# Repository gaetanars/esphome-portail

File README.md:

# esphome-portail

Pilotage d'un portail battant **FAAC E045S** avec un ESP32 sous [ESPHome](https://esphome.io) : commande
ouvrir / fermer / stop / ouverture piéton, et retour d'état et de position dans Home Assistant, y compris pour les
mouvements déclenchés par la télécommande ou un bouton.

> ⚠️ **Sécurité** : la carte et la sortie LAMP sont en **230 V~**. Coupez l'alimentation avant toute intervention
> et faites intervenir une personne qualifiée. Un portail motorisé est une machine dangereuse : vérifiez le
> fonctionnement des sécurités (cellules, détection d'obstacle) après toute modification.

## Matériel

- ESP32 de type WROOM / `esp32dev` (GPIO16/17 sont indisponibles sur les modules WROVER à PSRAM).
- 2 relais (contact NO) : simulent les entrées OP-A et OP-B.
- 1 optocoupleur compatible 24 V : lit la sortie W.L.
- 1 module de détection 230 V (isolé) : lit la sortie LAMP.

### Exemples de références

Exemples non exhaustifs, à vérifier (tension, brochage, logique) avant achat : aucun n'est imposé.

| Rôle | Exemples |
|---|---|
| ESP32 | Espressif ESP32-DevKitC-32E (module WROOM-32E), ESP32 DevKit V1 (DOIT) – tout module WROOM sur carte `esp32dev` |
| Relais OP-A / OP-B | Module 2 relais 5 V à optocoupleur (relais SRD-05VDC-SL-C, contact NO) ; ou relais miniature 5 V + transistor |
| Lecture W.L. (24 V) | Module optocoupleur PC817 / EL817 (entrée 3,6–30 V, sortie collecteur vers GPIO) |
| Lecture LAMP (230 V~) | Module de détection tension secteur à optocoupleur (« AC 220 V optocoupler isolation board », sortie 3,3–5 V) ; ou relais miniature à bobine 230 V~ (famille Finder 40.31) dont le contact NO est lu par le GPIO |
| Alimentation ESP32 | Depuis la sortie 24 V de la carte (J9 – 17/18) via un convertisseur abaisseur 24 V → 5 V (MP1584, LM2596) ; ou module secteur isolé Hi-Link HLK-PM01 (5 V) |

Points d'attention :

- Beaucoup de modules relais sont **actifs à l'état bas** : vérifier la fiche et ajouter `inverted: true` sur les `switch` si besoin.
- Les modules d'entrée doivent être **isolés galvaniquement** (optocoupleur) ; ne jamais relier le 230 V ni le 24 V directement à un GPIO.
- Les capteurs analogiques de tension (type ZMPT101B) ne conviennent pas : il faut une sortie logique tout ou rien.
- Si la sortie du module est active à l'état haut, adapter `inverted` sur les `binary_sensor` `wl` et `lamp`.

## Câblage

Notice FAAC E045S, réf. 532373 Rev.A, FW 4.0 (non redistribuée : copyright FAAC, `docs/*.pdf` est ignoré par git).

| Fonction | Borne carte | Côté ESP32 | GPIO |
|---|---|---|---|
| OP-A (ouverture totale) | J3 – 9 | relais A, NO | GPIO16 |
| OP-B (ouverture piéton) | J3 – 10 | relais B, NO | GPIO17 |
| Commun « - » des commandes | J9 – 15/16 | commun des relais | – |
| W.L. (collecteur ouvert, 24 V 3 W, 100 mA max) | J11 – 20 | optocoupleur (+24 V : J9 – 17/18) | GPIO25 |
| LAMP (230 V~ 60 W) | J2 – 7/8 | module de détection 230 V | GPIO26 |

Les broches se changent via les `substitutions` de `portail.yaml`.

## Carte dédiée (optionnel)

`hardware/` contient une carte unique (KiCad 10) qui remplace les modules du commerce : ESP32-WROOM-32UE (antenne
déportée), 2 relais, optos W.L. et LAMP, alimentation 24 V → 5 V → 3,3 V et USB-C pour le premier flash. Le brochage
reste celui de `portail.yaml` (GPIO16/17/25/26) : aucun changement de firmware. Voir `hardware/README.md`.

## Réglages requis sur la carte

| Paramètre | Valeur | Raison |
|---|---|---|
| `Lo` (logique) | `E` ou `EP` | Seules logiques supportées (OPEN stoppe/inverse). `A`/`AP`/`SP` : fermeture auto non pilotée ; `b`/`C` : non supportées. |
| `Sp` (sortie W.L.) | `00` (défaut) | Fixe = ouverture/ouvert/pause, clignotante = fermeture, éteinte = fermé. |
| `PF` (préclignotement) | `no` de préférence | Évite un décalage entre commande et mouvement. |
| `tA` | indifférent | Absorbé par le calibrage des durées. |

## Principe de lecture d'état

- **LAMP** active = le portail bouge.
- **W.L.** donne le sens : fixe = ouverture, clignotante = fermeture, éteinte (à l'arrêt) = fermé.
- La position est intégrée dans le temps à partir des mouvements observés, et recalée à 0 % à chaque fermeture.
- Les commandes sont en boucle fermée : impulsion, observation du sens réel, correction si nécessaire.

## Entités exposées

- `cover` Portail (ouvrir / fermer / stop, position), bouton **Ouverture piéton**, capteur texte **État**.
- Diagnostic : **Durée dernier mouvement**, **Signal Wi-Fi**, **Uptime**, **Statut**, bouton **Redémarrer**.

## Calibrage des durées

Effectuer une course complète (totale, puis piéton) et lire le capteur **Durée dernier mouvement**, puis reporter
les valeurs dans les substitutions `open_time_total`, `close_time_total`, `open_time_partial`, `close_time_partial`.

## Installation

```sh
python3 -m venv .venv && .venv/bin/pip install -r requirements.txt
cp secrets.yaml.example secrets.yaml   # puis renseigner les vraies valeurs
.venv/bin/esphome config portail.yaml  # validation
.venv/bin/esphome run portail.yaml     # compile + flash (premier flash en USB)
```

Clé API : `openssl rand -base64 32`. Les valeurs de `secrets.yaml.example` sont factices (utilisées par la CI).

## Limites connues

- `has_position: true` sans `position_action` : le curseur de position de Home Assistant n'agit que sur 0 % / 100 %.
- La position est estimée (temps), pas mesurée : elle se recale uniquement à la fermeture.
- En mode piéton (2 moteurs), seul le vantail M1 s'ouvre : affiché à 50 %.

## Développement

```sh
pre-commit install
pre-commit run --all-files
```

La CI (GitHub Actions) lance le lint, `esphome config` et `esphome compile`.

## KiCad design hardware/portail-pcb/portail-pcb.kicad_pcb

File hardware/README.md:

# Carte ESP32 pour portail FAAC E045S

Carte 2 couches (108 × 80 mm, FR4 1,6 mm, ENIG), composants sur la face supérieure, assemblage complet PCBWay.
Brochage identique à `portail.yaml` : relais GPIO16/17 (actifs à l'état haut), W.L. GPIO25 et LAMP GPIO26 (actifs à l'état bas).

> **État : prototype non fabriqué, non testé.** ERC/DRC passent, mais aucune simulation ni essai physique.

## Vérification du BOM (11/11/2026)

Contrôle sur pages publiques de distributeurs (LCSC, DigiKey, Mouser, Arrow), liens dans `portail-bom.csv`. **Le stock de la
bibliothèque PCBWay elle-même n'est pas interrogeable sans compte** : à confirmer dans l'outil de devis PCBWay (les parts
absentes de leur stock sont sourcées chez eux ou à fournir en consignation).

Remplacements faits après contrôle : bornier Degson DG128-5.0 (pas **5,00** mm) → DG500-5.08 ; EL817S (rupture LCSC) → LTV-817S ;
LED Everlight 19-217 (arrêtée) → Hubei KENTO KT-0603 ; 10 µF/50 V Samsung (brokers seulement) → Murata ; RC2512 (aucun stock
fiable) → Yageo SR2512 (±20 %, 200 V de service chacune) ; SS26/SS14 unifiées en SS36.

Points de vigilance : PTC MF-MSMF020/60-2 « Not For New Designs » chez DigiKey (stock OK ailleurs) ; SMBJ26CA peu de stock LCSC ;
C9 (CL10B105KA8NNNC) volatil, tout 1 µF X7R ≥ 10 V en 0603 convient ; empreinte des borniers = Phoenix MKDS 5,08 générique,
**à confronter à la datasheet Degson DG500** (perçage, encombrement). Non contrôlés un par un : résistances/condensateurs Yageo 0603.

## Raccordement (pas 5,08 mm)

| Bornier | Broches | Vers FAAC |
|---|---|---|
| J1 | +24V / GND / W.L. | J9-17 / J9-15 / J11-20 |
| J2 | OP-A / OP-B / COM | J3-9 / J3-10 / J9-16 |
| J3 (230 V~) | L / N | J2-7 / J2-8 |

Alimentation : 24 V de J9 (500 mA max pour tous les accessoires). Fusible PTC 0,2 A sur la carte.

## Choix de conception à connaître

- Buck **LMR16006Y** (4–40 V, 0,6 A) : asynchrone, d'où la diode de roue libre D2. Schéma de référence TI (54,9 k / 10 k pour 5 V).
- TVS SMBJ26CA : écrête vers ~42 V, sous le maximum absolu du buck (65 V) mais au-dessus de sa plage de service (40 V).
- 5 V = buck OU VBUS USB (diodes Schottky) : flash possible sans 24 V. CH340C alimenté en 3,3 V (V3 relié à VCC) ; ERC signale
  ce raccordement en avertissement (`pin_to_pin`), c'est voulu.
- LAMP : 2 × 51 k (2512) en série → ~3 mA crête dans l'opto AC LTV-814 ; l'ondulation 50 Hz est filtrée par `lamp_off_delay`.
- Isolation 230 V : fente fraisée sous l'opto, 6 mm mini entre le net `HV230` et le reste (règle `.kicad_dru`), pas de cuivre de
  masse dans la zone. **Aucune certification** : à valider avant usage sur secteur.
- Relais : contacts secs entre OP-A/OP-B et COM.

## Régénérer / exporter

Prérequis : KiCad 10, openjdk, et le `.jar` Freerouting (release GitHub officielle) placé hors du dépôt.

```sh
hardware/scripts/build.sh /chemin/vers/freerouting.jar   # schéma + placement + routage + zones
hardware/scripts/export.sh                                 # Gerbers, perçages, placement, BOM -> hardware/production/
hardware/scripts/render.sh                                 # rendus PNG/SVG pour relecture
```

Source unique : `scripts/design.py` (composants, nets), `scripts/place.py` (placement).

## Commande PCBWay

1. PCB : uploader `production/portail-gerber.zip` ; 2 couches, 108 × 80 mm, 1,6 mm, finition ENIG, vernis vert, sérigraphie
   blanche. Vérifier la fente fraisée (couche Edge.Cuts) dans la visionneuse. Option conseillée : vernis de tropicalisation.
2. Assemblage : « Turnkey », face supérieure ; uploader `production/portail-bom.csv` et `production/portail-pos.csv`
   (coordonnées en mm ; Y négatif = convention KiCad, à valider dans l'aperçu PCBWay).
3. **Antenne non soudée** : commander à part un pigtail U.FL → SMA traversée de boîtier et une antenne 2,4 GHz 3–5 dBi.
4. Les relais, borniers, varistance et optos traversants/CMS sont assemblés par PCBWay (vérifier la disponibilité de chaque MPN).

## Premier essai (sans flasher depuis l'outil)

1. Contrôle visuel, puis mesure de continuité GND / 24 V / 5 V / 3,3 V à l'ohmmètre.
2. Mise sous tension **24 V seul** (sans 230 V, sans W.L.) : 5 V puis 3,3 V attendus, LED verte allumée.
3. Premier flash par USB-C (BOOT/RESET manuels si l'auto-reset échoue), puis raccordement W.L., commandes, et en dernier 230 V.

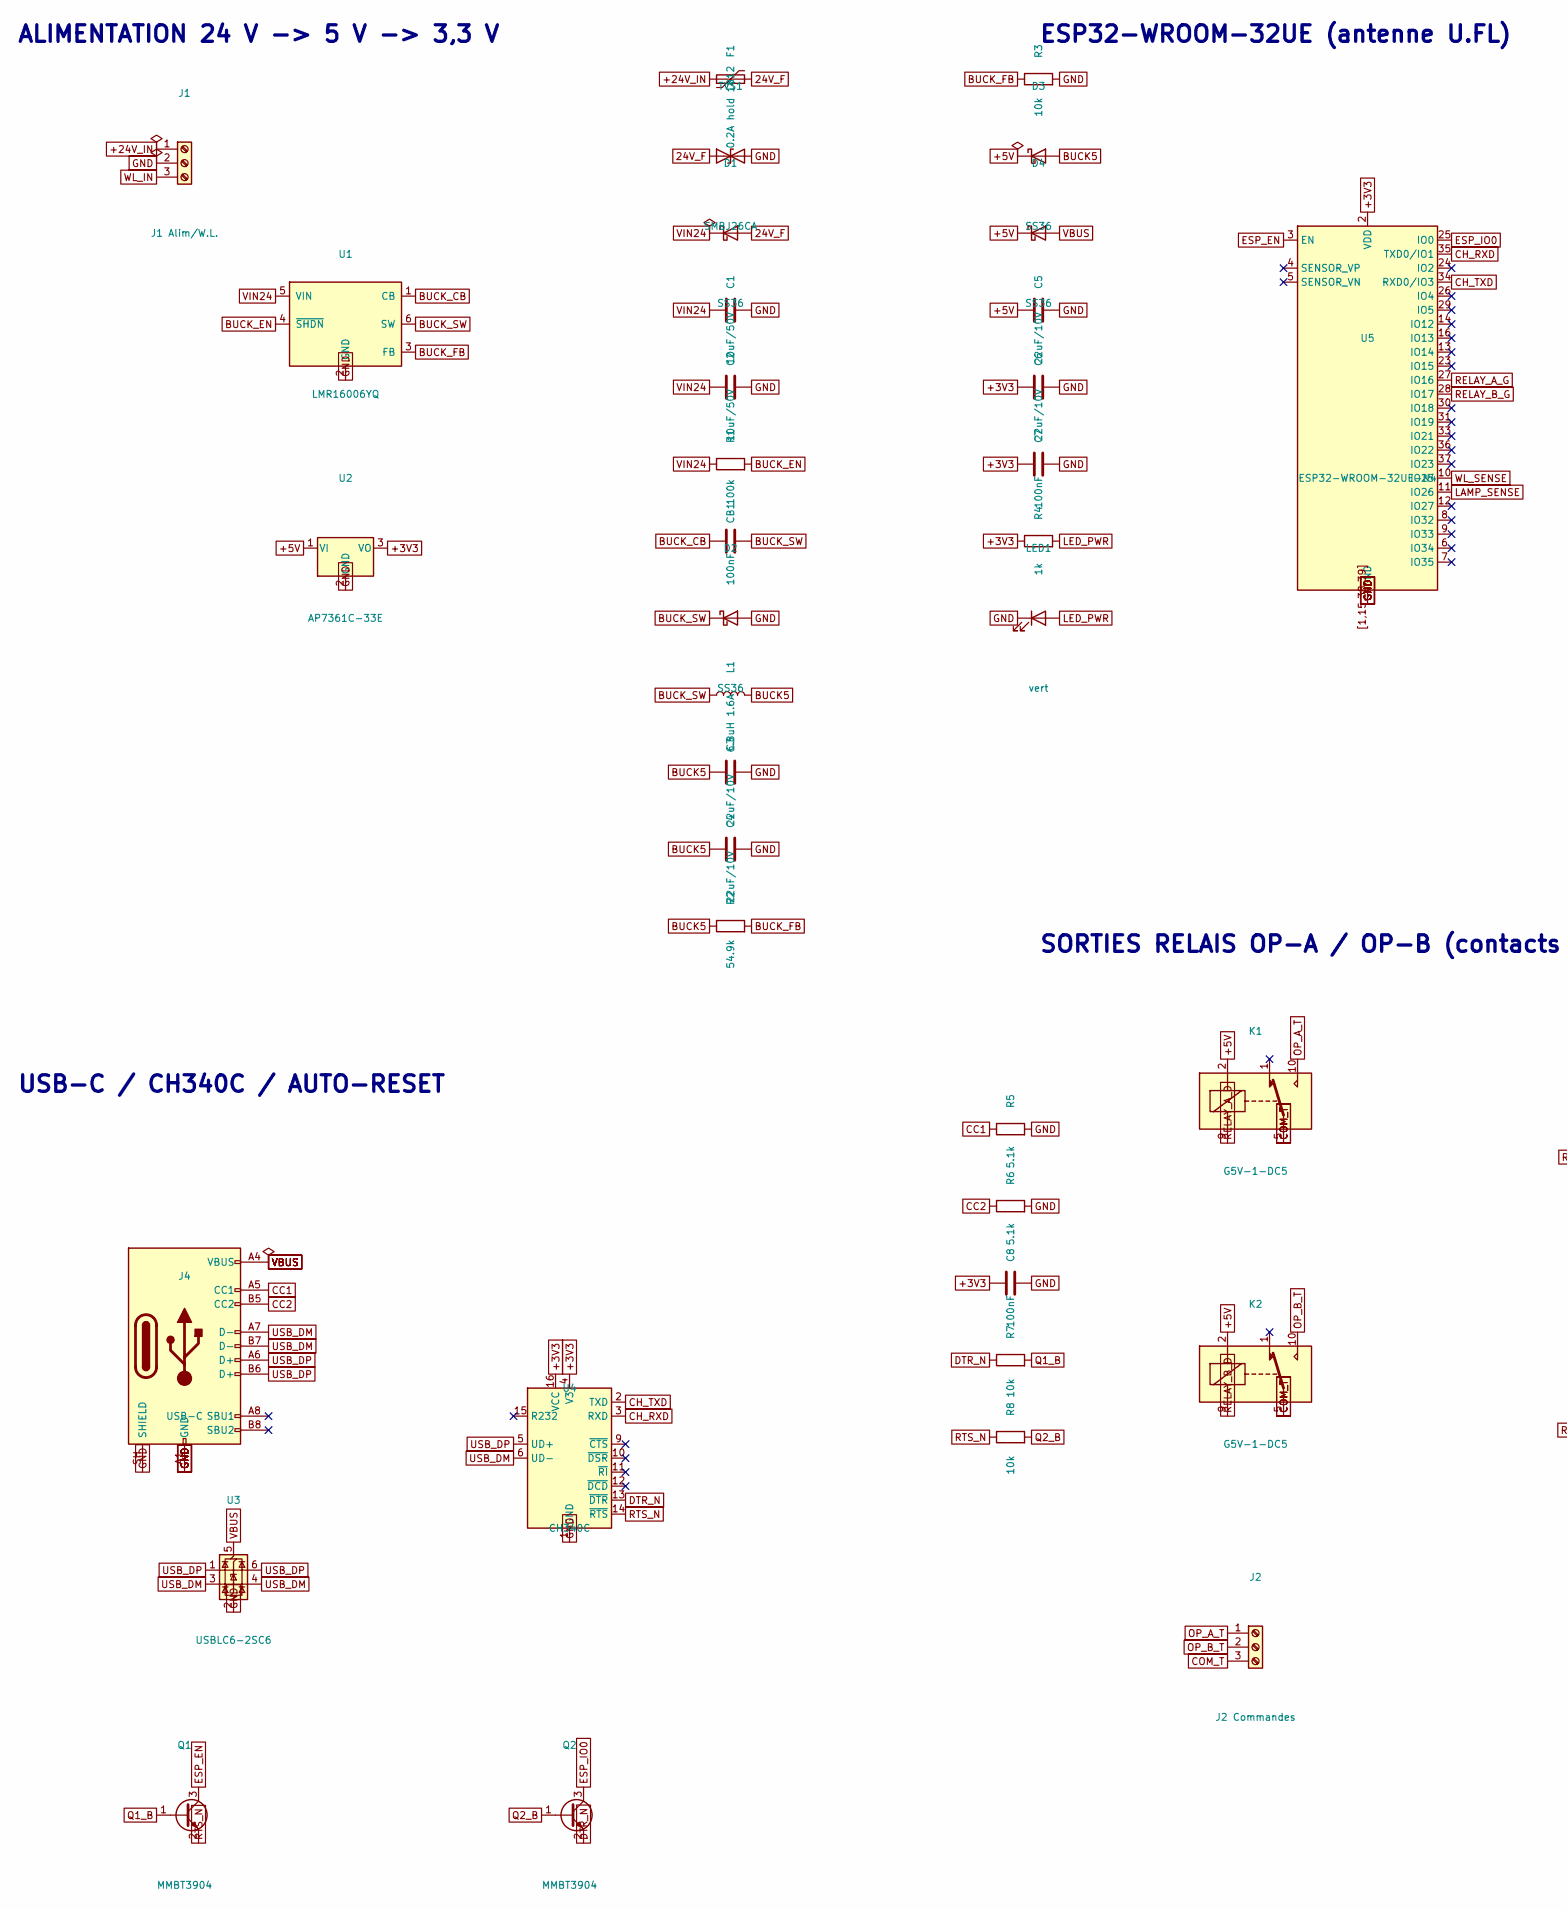
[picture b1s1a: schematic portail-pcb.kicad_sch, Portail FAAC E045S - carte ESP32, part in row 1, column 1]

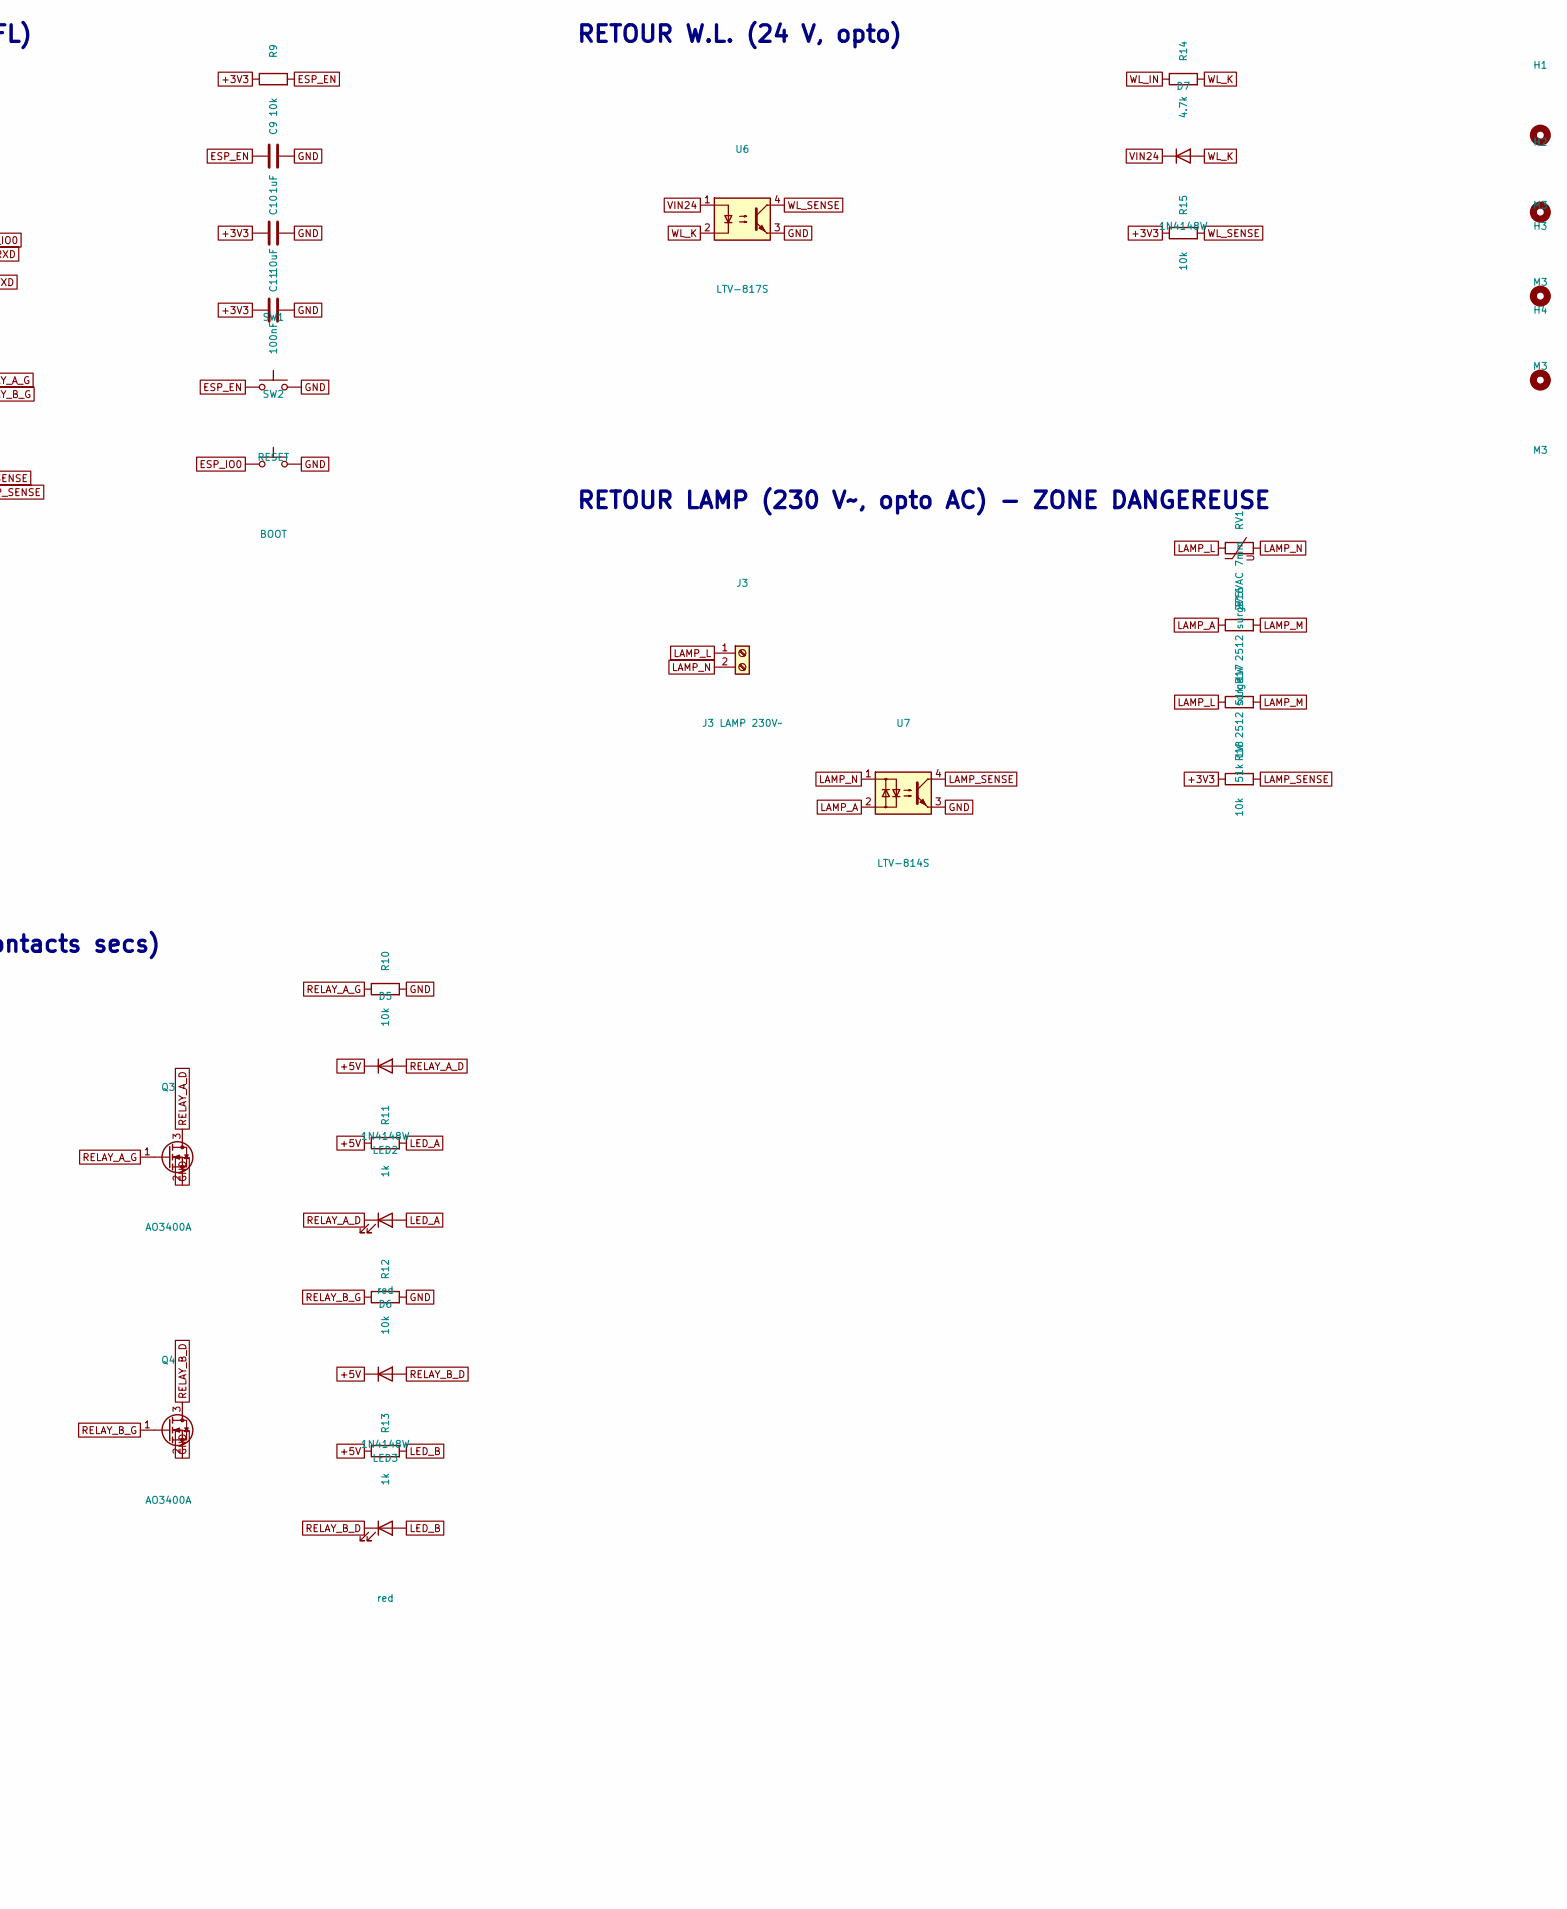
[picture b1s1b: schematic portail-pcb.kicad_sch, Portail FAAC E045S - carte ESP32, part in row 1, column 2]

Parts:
C1, C2: 10uF/50V; C_1210_3225Metric; MPN GRM32ER71H106KA12L
C3, C4, C5, C6: 22uF/10V; C_0805_2012Metric; MPN CL21A226MPQNNNE
C7, C8, C11: 100nF; C_0603_1608Metric; MPN CC0603KRX7R9BB104
C9: 1uF; C_0603_1608Metric; MPN CL10B105KA8NNNC
C10: 10uF; C_0805_2012Metric; MPN CL21A106KAYNNNE
CB1: 100nF; C_0603_1608Metric; MPN CC0603KRX7R9BB104
D1, D2, D3, D4: SS36; D_SMA; MPN SS36
D5, D6, D7: 1N4148W; D_SOD-123; MPN 1N4148W-7-F
F1: 0.2A hold 1812; Fuse_1812_4532Metric; MPN MF-MSMF020/60-2
H1, H2, H3, H4: M3; MountingHole_3.2mm_M3
J1: J1 Alim/W.L.; TerminalBlock_Phoenix_MKDS-1,5-3-5.08_1x03_P5.08mm_Horizont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; MPN DG500-5.08-03P-14-00A(H)
J2: J2 Commandes; TerminalBlock_Phoenix_MKDS-1,5-3-5.08_1x03_P5.08mm_Horizont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; MPN DG500-5.08-03P-14-00A(H)
J3: J3 LAMP 230V~; TerminalBlock_Phoenix_MKDS-1,5-2-5.08_1x02_P5.08mm_Horizont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; MPN DG500-5.08-02P-14-00A(H)
J4: USB-C; USB_C_Receptacle_HRO_TYPE-C-31-M-12; MPN TYPE-C-31-M-12
K1, K2: G5V-1-DC5; Relay_SPDT_Omron_G5V-1; MPN G5V-1-DC5
L1: 6.8uH 1.6A; L_Bourns_SRN6045TA; MPN SRN6045TA-6R8M
LED1: vert; LED_0603_1608Metric; MPN KT-0603G
LED2, LED3: red; LED_0603_1608Metric; MPN KT-0603R
Q1, Q2: MMBT3904; SOT-23; MPN MMBT3904LT1G
Q3, Q4: AO3400A; SOT-23; MPN AO3400A
R1: 100k; R_0603_1608Metric; MPN RC0603FR-07100KL
R2: 54.9k; R_0603_1608Metric; MPN RC0603FR-0754K9L
R3, R7, R8, R9, R10, R12, R15, R18: 10k; R_0603_1608Metric; MPN RC0603FR-0710KL
R4, R11, R13: 1k; R_0603_1608Metric; MPN RC0603FR-071KL
R5, R6: 5.1k; R_0603_1608Metric; MPN RC0603FR-075K1L
R14: 4.7k; R_0603_1608Metric; MPN RC0603FR-074K7L
R16, R17: 51k 1W 2512 surge; R_2512_6332Metric; MPN SR2512MK-0751KL
RV1: 275VAC 7mm; RV_Disc_D7mm_W3.4mm_P5mm; MPN V275LA4P
SW1: RESET; SW_SPST_TL3342; MPN TS-1187A-B-A-B
SW2: BOOT; SW_SPST_TL3342; MPN TS-1187A-B-A-B
TVS1: SMBJ26CA; D_SMB; MPN SMBJ26CA
U1: LMR16006YQ; SOT-23-6; MPN LMR16006YQDDCRQ1
U2: AP7361C-33E; SOT-223-3_TabPin2; MPN AP7361C-33E-13
U3: USBLC6-2SC6; SOT-23-6; MPN USBLC6-2SC6
U4: CH340C; SOIC-16_3.9x9.9mm_P1.27mm; MPN CH340C
U5: ESP32-WROOM-32UE-N4; ESP32-WROOM-32UE; MPN ESP32-WROOM-32UE-N4
U6: LTV-817S; SMDIP-4_W9.53mm; MPN LTV-817S-TA1
U7: LTV-814S; SMDIP-4_W9.53mm; MPN LTV-814S-TA1

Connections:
24V_F: D1.2 (A), F1.2, TVS1.1 (A1)
+3V3: C6.1, C7.1, C8.1, C10.1, C11.1, R4.1, R9.1, R15.1, R18.1, U2.3 (VO), U4.4 (V3), U4.16 (VCC), U5.2 (VDD)
+5V: C5.1, D3.1 (K), D4.1 (K), D5.1 (K), D6.1 (K), K1.2, K2.2, R11.1, R13.1, U2.1 (VI)
+24V_IN: F1.1, J1.1
BUCK5: C3.1, C4.1, D3.2 (A), L1.2, R2.1
BUCK_CB: CB1.1, U1.1 (CB)
BUCK_EN: R1.2, U1.4 (~SHDN)
BUCK_FB: R2.2, R3.1, U1.3 (FB)
BUCK_SW: CB1.2, D2.1 (K), L1.1, U1.6 (SW)
CC1: J4.A5 (CC1), R5.1
CC2: J4.B5 (CC2), R6.1
CH_RXD: U4.3 (RXD), U5.35 (TXD0/IO1)
CH_TXD: U4.2 (TXD), U5.34 (RXD0/IO3)
COM_T: J2.3, K1.5, K1.6, K2.5, K2.6
DTR_N: Q2.2 (E), R7.1, U4.13 (~DTR)
ESP_EN: C9.1, Q1.3 (C), R9.2, SW1.1, U5.3 (EN)
ESP_IO0: Q2.3 (C), SW2.1, U5.25 (IO0)
GND: C1.2, C2.2, C3.2, C4.2, C5.2, C6.2, C7.2, C8.2, C9.2, C10.2, C11.2, D2.2 (A), J1.2, J4.A1 (GND), J4.A12 (GND), J4.B1 (GND), J4.B12 (GND), J4.SH (SHIELD), LED1.1 (K), Q3.2 (S), Q4.2 (S), R3.2, R5.2, R6.2, R10.2, R12.2, SW1.2, SW2.2, TVS1.2 (A2), U1.2 (GND), U2.2 (GND), U3.2 (GND), U4.1 (GND), U5.1, U5.15, U5.38, U5.39, U5.[1,15,38,39] (GND), U6.3, U7.3
LAMP_A: R16.1, U7.2
LAMP_L: J3.1, R17.1, RV1.1
LAMP_M: R16.2, R17.2
LAMP_N: J3.2, RV1.2, U7.1
LAMP_SENSE: R18.2, U5.11 (IO26), U7.4
LED_A: LED2.2 (A), R11.2
LED_B: LED3.2 (A), R13.2
LED_PWR: LED1.2 (A), R4.2
OP_A_T: J2.1, K1.10
OP_B_T: J2.2, K2.10
Q1_B: Q1.1 (B), R7.2
Q2_B: Q2.1 (B), R8.2
RELAY_A_D: D5.2 (A), K1.9, LED2.1 (K), Q3.3 (D)
RELAY_A_G: Q3.1 (G), R10.1, U5.27 (IO16)
RELAY_B_D: D6.2 (A), K2.9, LED3.1 (K), Q4.3 (D)
RELAY_B_G: Q4.1 (G), R12.1, U5.28 (IO17)
RTS_N: Q1.2 (E), R8.1, U4.14 (~RTS)
USB_DM: J4.A7 (D-), J4.B7 (D-), U3.3 (I/O2), U3.4 (I/O2), U4.6 (UD-)
USB_DP: J4.A6 (D+), J4.B6 (D+), U3.1 (I/O1), U3.6 (I/O1), U4.5 (UD+)
VBUS: D4.2 (A), J4.A4 (VBUS), J4.A9 (VBUS), J4.B4 (VBUS), J4.B9 (VBUS), U3.5 (VBUS)
VIN24: C1.1, C2.1, D1.1 (K), D7.1 (K), R1.1, U1.5 (VIN), U6.1
WL_IN: J1.3, R14.1
WL_K: D7.2 (A), R14.2, U6.2
WL_SENSE: R15.2, U5.10 (IO25), U6.4

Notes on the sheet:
ALIMENTATION 24 V -> 5 V -> 3,3 V
USB-C / CH340C / AUTO-RESET
ESP32-WROOM-32UE (antenne U.FL)
SORTIES RELAIS OP-A / OP-B (contacts secs)
RETOUR W.L. (24 V, opto)
RETOUR LAMP (230 V~, opto AC) - ZONE DANGEREUSE

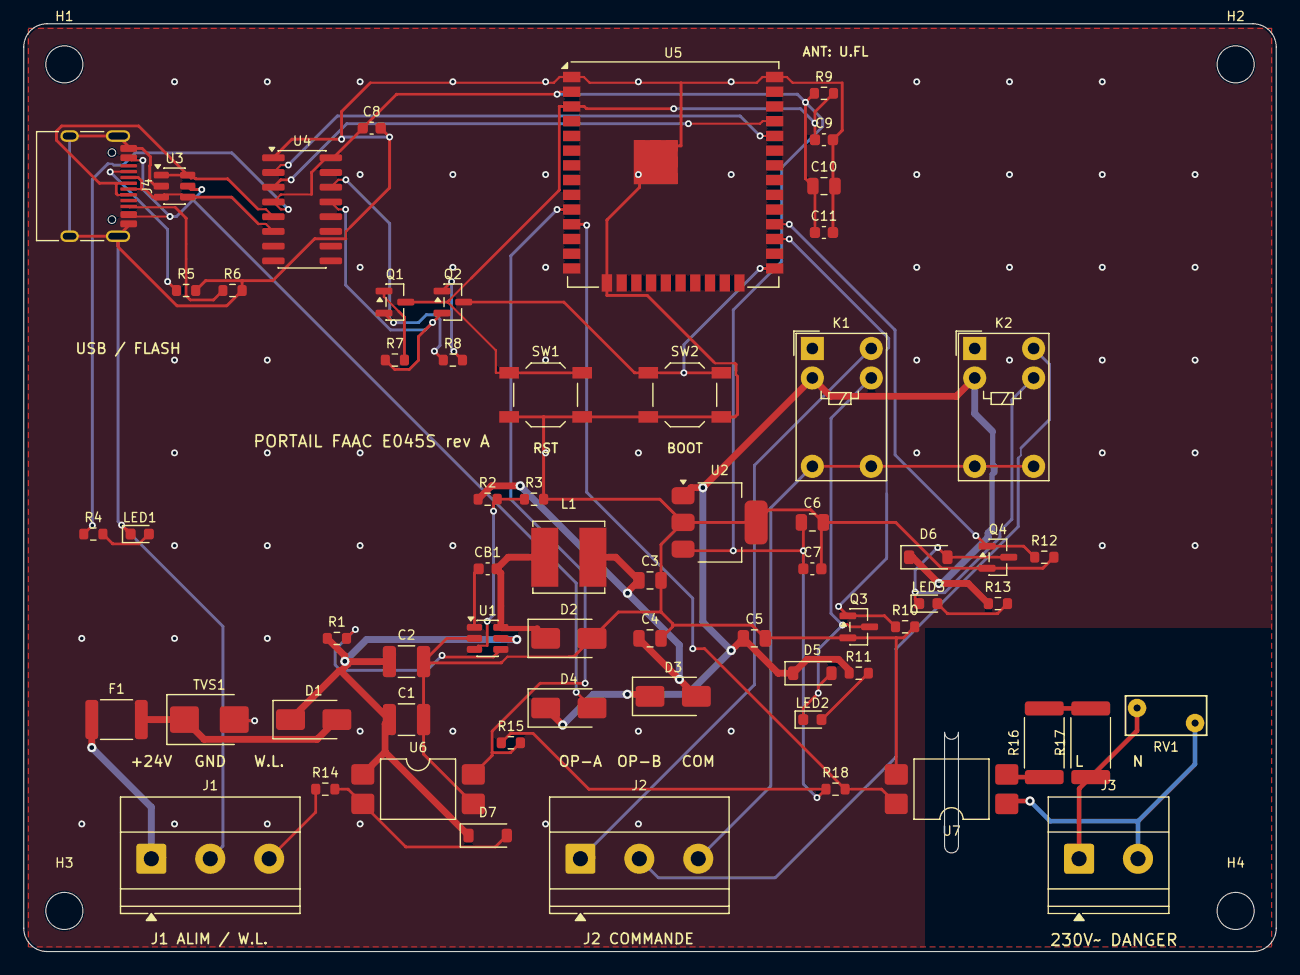
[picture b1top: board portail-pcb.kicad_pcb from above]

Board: 2 copper layers, 108.0 x 80.0 mm, 67 parts (0 on the bottom side), 42 nets.
